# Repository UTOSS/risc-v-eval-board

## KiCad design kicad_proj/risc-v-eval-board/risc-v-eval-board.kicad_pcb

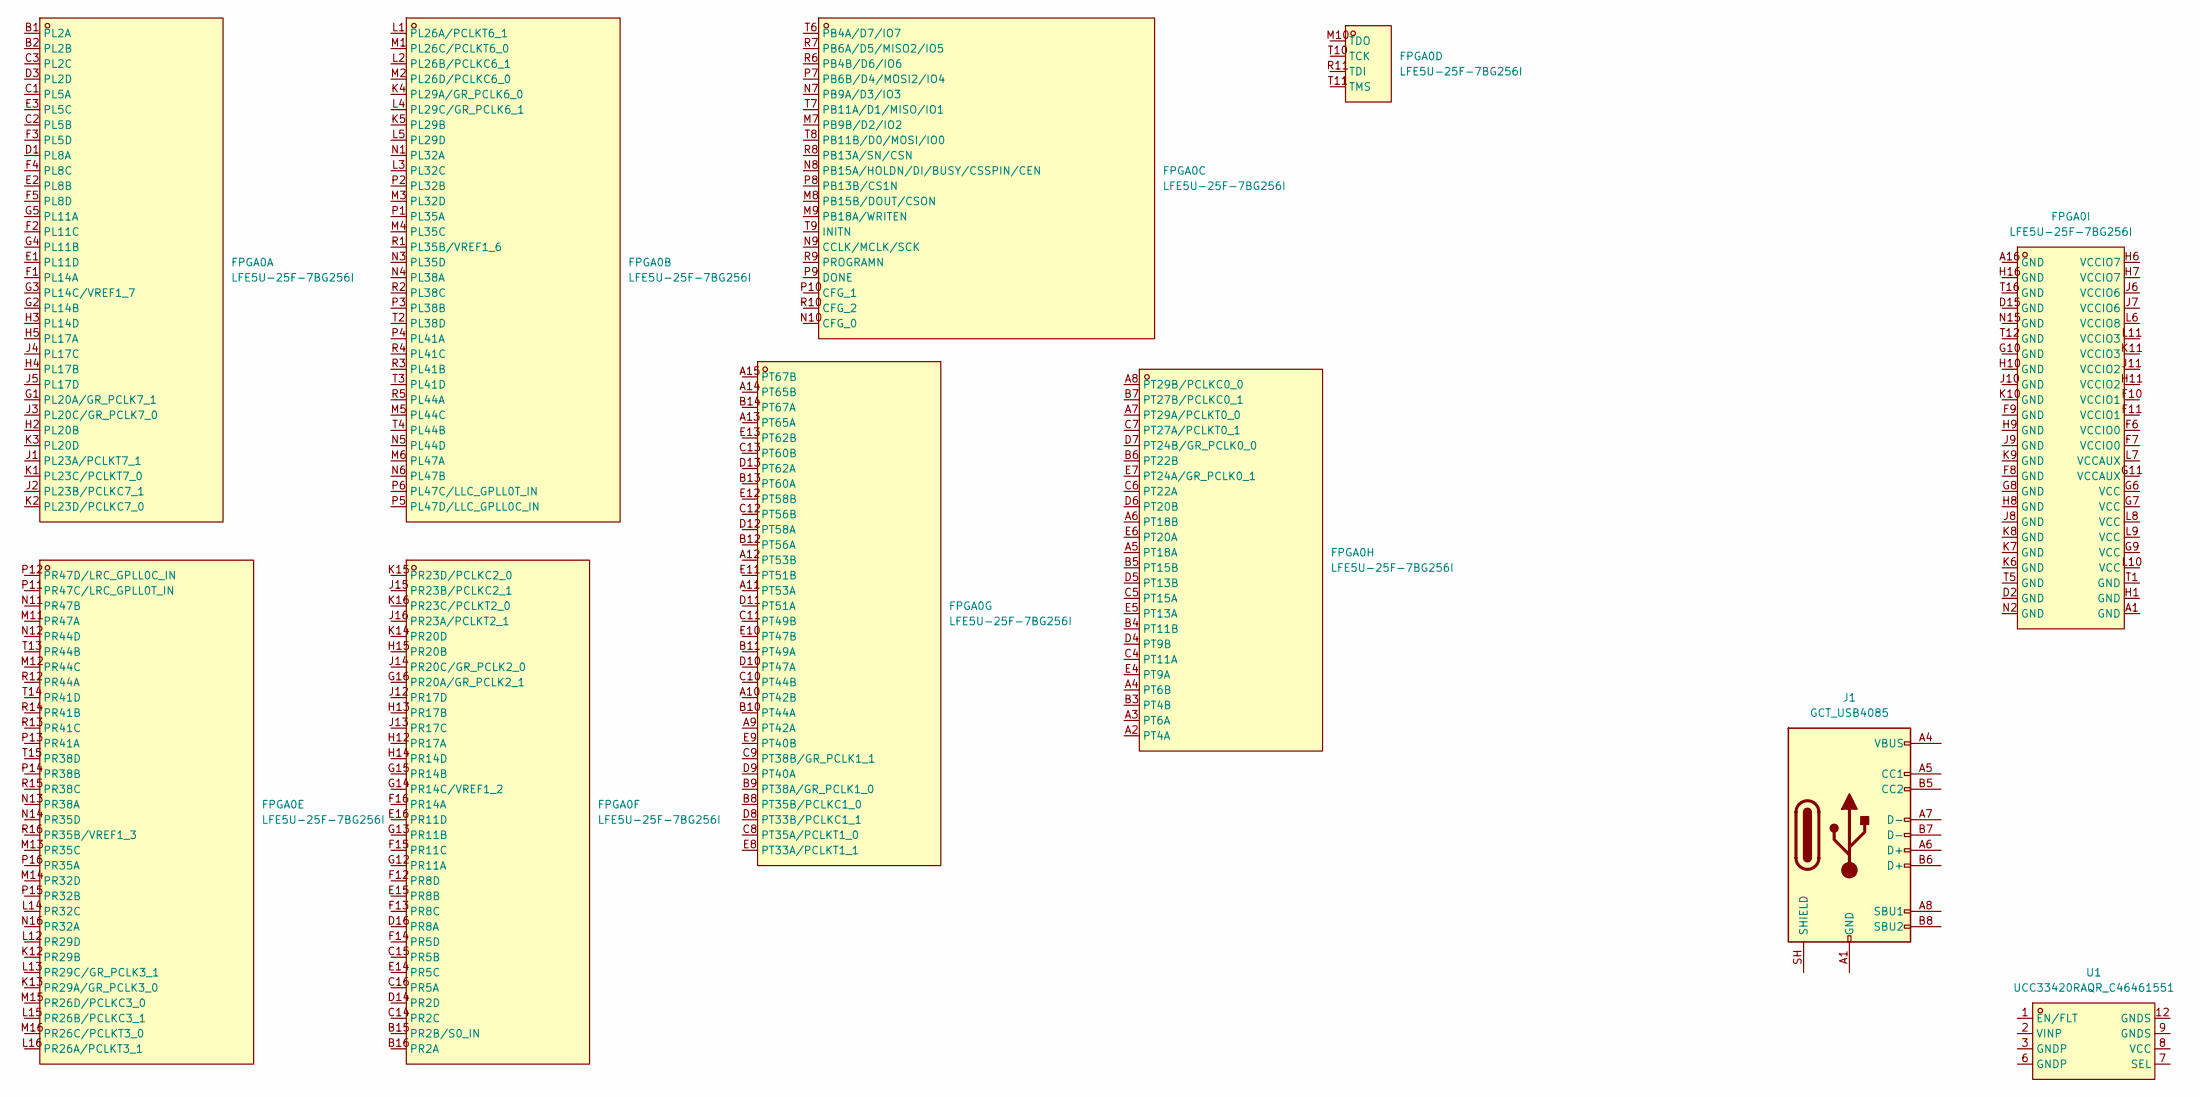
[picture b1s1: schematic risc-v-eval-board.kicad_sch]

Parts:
FPGA0: LFE5U-25F-7BG256I; CABGA-256_L14.0-W14.0-R16-C16-P0.80-TL; MPN LFE5U-25F-7BG256I; LCSC Part C1550762
J1: GCT_USB4085; USB_C_Receptacle_GCT_USB4085
U1: UCC33420RAQR_C46461551; VSON-12_L5.0-W4.0-P0.65-TL_PUCC33420QRAQRQ1; MPN UCC33420RAQR; LCSC Part C46461551

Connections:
unnamed: J1.A1 (GND), J1.A12 (GND), J1.B1 (GND), J1.B12 (GND)
unnamed: J1.A4 (VBUS), J1.A9 (VBUS), J1.B4 (VBUS), J1.B9 (VBUS)

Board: 2 copper layers, 7 parts (0 on the bottom side), 2 nets, no tracks yet.

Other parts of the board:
H1, H2, H3, H4: MountingHole_3.2mm_M3
